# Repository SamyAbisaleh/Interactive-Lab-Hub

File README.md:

# Interactive-Lab-Hub

Completed Labs for Samy Abisaleh -- Student

1. [Samy A's Lab 1](https://github.com/SamyAbisaleh/Interactive-Lab-Hub/tree/master/Lab%201)
2. [Samy A's Lab 2](https://github.com/SamyAbisaleh/Interactive-Lab-Hub/tree/master/Lab%202)
3. [Samy A's Lab 3](https://github.com/SamyAbisaleh/Interactive-Lab-Hub/tree/master/Lab%203)
4. [Samy A's Lab 5](https://github.com/SamyAbisaleh/Interactive-Lab-Hub/tree/master/Alt-Lab%20%235)
5. [Samy A's Lab 6](https://github.com/SamyAbisaleh/Interactive-Lab-Hub/tree/master/Lab-6)
6. [Samy A's Lab 7](https://github.com/SamyAbisaleh/Interactive-Lab-Hub/blob/master/Lab-7)
7. [Samy A's Final Project](https://github.com/SamyAbisaleh/Interactive-Lab-Hub/tree/master/Final%20Project)

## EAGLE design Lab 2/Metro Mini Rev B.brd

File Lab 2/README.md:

# Alt-Lab #2
## Pre-Lab
### Idea Generation
[Click to access the Ideas generated as a PDF ](https://github.com/SamyAbisaleh/Interactive-Lab-Hub/blob/master/Lab%202/Pre-Lab.pdf)
 
## Overview
For this assignment, you are going to 

A) [Design your Arduino+](#part-a-design-your-arduino) 

B) [Order parts for your Arduino+](#part-b-order-parts-for-your-arduino) 

C) [Prototype your Arduino+](#part-c-prototype-your-arduino)

D) [Layout your Arduino+](#part-d-layout-your-arduino) 

E) [Send your board off to be made](#part-e-send-your-board-off-to-be-made)

## Part A. Design your Arduino+
Please document the design of your Arduino+:

**a) What is the + improvement of your Arduino+**
In this repo you will find the original files from Adafruit for the Metro Mini and a file I have edited. You can compare the changes to the schematic and the board file to see which changes were made.

I've decided I want to be able to read the temperature from my Metro Mini and have that be a part of the board itself. This requires adding an Temperature Sensor. I am using a surface mount [component](https://app.ultralibrarian.com/details/1690C20E-103F-11E9-AB3A-0A3560A4CCCC/Texas-Instruments/TMP102AIDRLRG4?ref=digikey)

**b) What Arduino form-factor/design are you basing your design off of?**
* My design is based off of the Metro Mini, the files I started with can be found: [here](https://github.com/SamyAbisaleh/Interactive-Lab-Hub/tree/master/Lab%202/Metro%20Mini%20Files/Adafruit-METRO-328-PCB-master/Adafruit-METRO-328-PCB-master)

**c) What features/parts need to be incorporated for your Arduino+? Include your research!**
Based on the datasheet there are multiple things that needed to be considered and added to my Arduino.
1. The entire Metro Mini must be operating at 3.3 V instead of 5V as the SDA and SCL pins cannot operate at 5V and it may cause damage to the sensor
2. The second important feature that I must incorporate is 2 5K resistors that buffer the SDA and SCL pins from the 3.3 Volts.
3. Finally, I must include a .01 uF capacitor to help prevent noise from impacting the sensor.

The schematic I based these decisions off of can be found below.

**d) What is the timeline for the overall development of your Arduino?**

Based on a quick look at PCBShopper, it seems as though the timeline for the development of my Arduino is about 7 days to be created. Overall the entire project will take about 2-3 weeks to be completed. 1 week to determine what I am working on, and designing what I am working on. 1-2 weeks to order, create, and ship my design.

**e) Which fabrication company are you using, what do you plan to order, and what is the design rationale for the selection?**

I already ordered all my parts and my PCB using the Aisler.net. The total cost was about 15 dollars with shipping. This is expected to come to me in about 1-2 Weeks. I used this selection because it is a US based company (shipping should not be delayed due to COVID), the prices were low (15 dollars for 3 boards), they will put the parts on the board for me (just upload BOM and assign your parts). I was very impressed with how simple the process was, and I hope that everything comes in working condition. 

## Part B. Order parts for your Arduino+

Develop a bill of materials for your Arduino +.

**Bill of Materials**
|   Part  	|           Value          	|           Device          	|             Package            	|            Description           	|                                      Notes                                     	|                                                                                                                                                                     Link to part                                                                                                                                                                    	|
|:-------:	|:------------------------:	|:-------------------------:	|:------------------------------:	|:--------------------------------:	|:------------------------------------------------------------------------------:	|:---------------------------------------------------------------------------------------------------------------------------------------------------------------------------------------------------------------------------------------------------------------------------------------------------------------------------------------------------:	|
|    AD   	|           20609          	|      HEADER-1X6ROUND      	|           1X06_ROUND           	|            PIN HEADER            	|                            Footprint for pin headers                           	| [Link](https://www.digikey.com/product-detail/en/harwin-inc/D01-9923246/952-2521-ND/3918909?utm_adgroup=Rectangular%20Connectors%20-%20Headers%2C%20Specialty%20Pin&utm_source=google&utm_medium=cpc&utm_campaign=Shopping_Product_Connectors%2C%20Interconnects&utm_term=&utm_content=Rectangular%20Connectors%20-%20Headers%2C%20Specialty%20Pin) 	|
|   AD1   	|           20609          	|      HEADER-1X6ROUND      	|           1X06_ROUND           	|            PIN HEADER            	|                            Footprint for pin headers                           	| [Link](https://www.digikey.com/product-detail/en/harwin-inc/D01-9923246/952-2521-ND/3918909?utm_adgroup=Rectangular%20Connectors%20-%20Headers%2C%20Specialty%20Pin&utm_source=google&utm_medium=cpc&utm_campaign=Shopping_Product_Connectors%2C%20Interconnects&utm_term=&utm_content=Rectangular%20Connectors%20-%20Headers%2C%20Specialty%20Pin) 	|
|    C1   	|           10uF           	| CAP_CERAMIC0805-NOOUTLINE 	|             0805-NO            	|        Ceramic Capacitors        	|            Decoupling Capacitor: smoothes longer changes in voltage            	|                                                                                                                        https://www.digikey.com/product-detail/en/GRM21BC81D106KE51L/490-10500-1-ND/5026426/?itemSeq=338642887                                                                                                                       	|
|    C2   	|           10uF           	| CAP_CERAMIC0805-NOOUTLINE 	|             0805-NO            	|        Ceramic Capacitors        	|            Decoupling Capacitor: smoothes longer changes in voltage            	|                                                                                                                        https://www.digikey.com/product-detail/en/GRM21BC81D106KE51L/490-10500-1-ND/5026426/?itemSeq=338642887                                                                                                                       	|
|    C3   	|           10uF           	| CAP_CERAMIC0805-NOOUTLINE 	|             0805-NO            	|        Ceramic Capacitors        	|           Decoupling Capacitor: smoothes longer variation in voltage           	|                                                                                                                        https://www.digikey.com/product-detail/en/GRM21BC81D106KE51L/490-10500-1-ND/5026426/?itemSeq=338642887                                                                                                                       	|
|    C4   	|           0.1uF          	| CAP_CERAMIC0805-NOOUTLINE 	|             0805-NO            	|        Ceramic Capacitors        	|        Decoupling Capacitor: smoothes high frequency changes in voltage        	|                                                                                                                         https://www.digikey.com/product-detail/en/C0805C104M3RACTU/399-8000-6-ND/3472531/?itemSeq=338642888                                                                                                                         	|
|    C5   	|           0.1uF          	|     CAP_CERAMIC_0805MP    	|             _0805MP            	|        Ceramic Capacitors        	| When the DTR changes from high to low the reset pin on the ATMega will go high 	|                                                                                                                         https://www.digikey.com/product-detail/en/C0805C104M3RACTU/399-8000-6-ND/3472531/?itemSeq=338642888                                                                                                                         	|
|    C6   	|           0.1uF          	| CAP_CERAMIC0805-NOOUTLINE 	|             0805-NO            	|        Ceramic Capacitors        	|        Decoupling Capacitor: smoothes high frequency changes in voltage        	|                                                                                                                         https://www.digikey.com/product-detail/en/C0805C104M3RACTU/399-8000-6-ND/3472531/?itemSeq=338642888                                                                                                                         	|
|    C8   	|           0.1uF          	| CAP_CERAMIC0805-NOOUTLINE 	|             0805-NO            	|        Ceramic Capacitors        	|        Decoupling Capacitor: smoothes high frequency changes in voltage        	|                                                                                                                         https://www.digikey.com/product-detail/en/C0805C104M3RACTU/399-8000-6-ND/3472531/?itemSeq=338642888                                                                                                                         	|
|   C10   	|           0.1uF          	| CAP_CERAMIC0805-NOOUTLINE 	|             0805-NO            	|        Ceramic Capacitors        	|        Decoupling Capacitor: smoothes high frequency changes in voltage        	|                                                                                                                         https://www.digikey.com/product-detail/en/C0805C104M3RACTU/399-8000-6-ND/3472531/?itemSeq=338642888                                                                                                                         	|
|   C12   	|           10uF           	| CAP_CERAMIC0805-NOOUTLINE 	|             0805-NO            	|        Ceramic Capacitors        	|            Decoupling Capacitor: smoothes longer changes in voltage            	|                                                                                                                        https://www.digikey.com/product-detail/en/GRM21BC81D106KE51L/490-10500-1-ND/5026426/?itemSeq=338642887                                                                                                                       	|
|   C13   	|           .01uF          	| CAP_CERAMIC0805-NOOUTLINE 	|             0805-NO            	|        Ceramic Capacitors        	|            Decoupling Capacitor: smoothes longer changes in voltage            	|                                                                                                                   https://www.mouser.com/ProductDetail/KEMET/CKC33C103KJGACTU?qs=sGAEpiMZZMuMW9TJLBQkXhX%2FY8cKkU6Pw0elzxufyyw%3D                                                                                                                   	|
|    D3   	|          MBR120          	|   DIODE-SCHOTTKYSOD-123   	|             SOD-123            	|               Diode              	|                           ESD protection for USB port                          	|                                                                                                                     https://www.digikey.com/product-detail/en/BAT60AE6327HTSA1/BAT60AE6327HTSA1CT-ND/1557845/?itemSeq=338642881                                                                                                                     	|
|    D4   	|          YELLOW          	|     LED0805_NOOUTLINE     	|     CHIPLED_0805_NOOUTLINE     	|                LED               	|                                  Indicator LED                                 	|                                                                                                                           https://www.digikey.com/product-detail/en/150080YS75000/732-4987-1-ND/4489925/?itemSeq=338642883                                                                                                                          	|
|    D5   	|          YELLOW          	|     LED0805_NOOUTLINE     	|     CHIPLED_0805_NOOUTLINE     	|                LED               	|                                  Indicator LED                                 	|                                                                                                                           https://www.digikey.com/product-detail/en/150080YS75000/732-4987-1-ND/4489925/?itemSeq=338642883                                                                                                                          	|
|   IOL   	|           20610          	|      HEADER-1X8ROUND      	|           1X08_ROUND           	|            PIN HEADER            	|                            Footprint for pin headers                           	|     https://www.digikey.com/product-detail/en/harwin-inc/D01-9923246/952-2521-ND/3918909?utm_adgroup=Rectangular%20Connectors%20-%20Headers%2C%20Specialty%20Pin&utm_source=google&utm_medium=cpc&utm_campaign=Shopping_Product_Connectors%2C%20Interconnects&utm_term=&utm_content=Rectangular%20Connectors%20-%20Headers%2C%20Specialty%20Pin     	|
|    L    	|            RED           	|     LED0805_NOOUTLINE     	|     CHIPLED_0805_NOOUTLINE     	|                LED               	|                                  Indicator LED                                 	|                                                                                                                           https://www.digikey.com/product-detail/en/LH+R974-LP-1/475-1415-1-ND/1802604/?itemSeq=338642877                                                                                                                           	|
|    ON   	|           GREEN          	|     LED0805_NOOUTLINE     	|     CHIPLED_0805_NOOUTLINE     	|                LED               	|                                  Indicator LED                                 	|                                                                                                                           https://www.digikey.com/product-detail/en/LG+R971-KN-1/475-1410-1-ND/1802598/?itemSeq=338642882                                                                                                                           	|
|  POWER1 	|           20610          	|      HEADER-1X870MIL      	|          1X08_ROUND_70         	|            PIN HEADER            	|                            Footprint for pin headers                           	|     https://www.digikey.com/product-detail/en/harwin-inc/D01-9923246/952-2521-ND/3918909?utm_adgroup=Rectangular%20Connectors%20-%20Headers%2C%20Specialty%20Pin&utm_source=google&utm_medium=cpc&utm_campaign=Shopping_Product_Connectors%2C%20Interconnects&utm_term=&utm_content=Rectangular%20Connectors%20-%20Headers%2C%20Specialty%20Pin     	|
|    R1   	|            5k            	|   RESISTOR0805_NOOUTLINE  	|             0805-NO            	|             Resistors            	|                                                                                	|                                                                                                                             https://www.digikey.com/product-detail/en/vishay-dale/PNM0402E5001BST1/541-1901-1-ND/4341858                                                                                                                            	|
|    R2   	|            1K            	|       RESISTOR_4PACK      	|         RESPACK_4X0603         	|   Resistor Packs (4 resistors)   	|                   4x resistor array to current limit the LEDs                  	|                                                                                                                         https://www.digikey.com/product-detail/en/742C083102JP/742C083102JPCT-ND/1124573/?itemSeq=338642869                                                                                                                         	|
|    R4   	|            5k            	|   RESISTOR0805_NOOUTLINE  	|             0805-NO            	|             Resistors            	|                                                                                	|                                                                                                                             https://www.digikey.com/product-detail/en/vishay-dale/PNM0402E5001BST1/541-1901-1-ND/4341858                                                                                                                            	|
|    R8   	|            10K           	|   RESISTOR0805_NOOUTLINE  	|             0805-NO            	|             Resistors            	|         Pullup resistor on reset pin: when you hit reset pulls pin high        	|                                                                                                                         https://www.digikey.com/product-detail/en/RC0805FR-0710KL/311-10.0KCRCT-ND/730482/?itemSeq=338642870                                                                                                                        	|
|   R11   	|            1K            	|   RESISTOR0805_NOOUTLINE  	|             0805-NO            	|             Resistors            	|           Allows you to use the RX pin on the board over CP2104 chip           	|                                                                                                                          https://www.digikey.com/product-detail/en/RC0805JR-071KL/311-1.0KARCT-ND/731165/?itemSeq=338642876                                                                                                                         	|
|  RESET  	|           KMR2           	|   SWITCH_TACT_SMT4.6X2.8  	|        BTN_KMR2_4.6X2.8        	|         SMT Tact Switches        	|                                  Reset Button                                  	|                                                                                                                                    https://www.digikey.com/product-detail/en/c-k/KMR211GLFS/401-1426-1-ND/550461                                                                                                                                    	|
|    U1   	|        MIC5225-5.0       	|        VREG_SOT23-5       	|             SOT23-5            	| SOT23-5 Fixed Voltage Regulators 	|                              5V Voltage Regulator                              	|                                                                                                                  https://www.digikey.com/product-detail/en/LP2985IM5-5.0%2fNOPB/LP2985IM5-5.0%2fNOPBCT-ND/334983/?itemSeq=338642872                                                                                                                 	|
|    U2   	|        ATMEGA328P        	|         ATMEGA328P        	|            MLF32-TH            	|            ATMEGA 328P           	|                                     BRAINZ                                     	|                                                                                                                         https://www.digikey.com/product-detail/en/ATMEGA328P-MU/ATMEGA328P-MU-ND/1914588/?itemSeq=338642865                                                                                                                         	|
|    U3   	|          CP2104          	|           CP2104          	|         QFN24_4MM_SMSC         	|    CP2104 - USB to UART Bridge   	|                          USB communication with ATMEGA                         	|                                                                                                                          https://www.digikey.com/product-detail/en/CP2104-F03-GMR/336-4146-1-ND/7650425/?itemSeq=338642880                                                                                                                          	|
|    U4   	|        MIC5225-3.3       	|        VREG_SOT23-5       	|             SOT23-5            	| SOT23-5 Fixed Voltage Regulators 	|                              3V Voltage Regulator                              	|                                                                                                                https://www.digikey.com/product-detail/en/LP2985IM5X-3.3%2fNOPB/LP2985IM5X-3.3%2fNOPBCT-ND/3527394/?itemSeq=338642873                                                                                                                	|
|    U5   	| TMP102AIDRLRG4DRL6_TEX-M 	|  TMP102AIDRLRG4DRL6_TEX-M 	|           DRL6_TEX-M           	|                                  	|                                                                                	|                                                                                                                          https://www.digikey.com/product-detail/en/texas-instruments/TMP102AIDRLRG4/296-52785-2-ND/1907044                                                                                                                          	|
| VSELECT 	|                          	|     SOLDERJUMPER_2WAY     	| SOLDERJUMPER_2WAY_OPEN_NOPASTE 	|        2-Way Solder Jumper       	|                                                                                	|                                                                                                                                                                                                                                                                                                                                                     	|
|    X1   	|           20329          	|     USB_MICRO_20329_V2    	|         4UCONN_20329_V2        	|          USB Connectors          	|                                  USB connector                                 	|                                                                                                                           https://www.digikey.com/product-detail/en/amphenol-icc-fci/10103594-0001LF/609-4050-1-ND/2350357                                                                                                                          	|
|    Y2   	|   CSTCE16M0V53-R0 16MHZ  	|        RESONATORMU        	|            RESONATOR           	|                                  	|                             Set ATMEGA clock speed                             	|                                                                                                                        https://www.digikey.com/product-detail/en/CSTNE16M0V530000R0/490-17948-1-ND/8747756/?itemSeq=338642875                                                                                                                       	|

## Part C. Prototype your Arduino+

To prototype my Arduino, I need to order a [Temperature Sensor](https://www.mouser.com/ProductDetail/Adafruit/3251?qs=DJieTMTAD3WAE3SOd7%2FRQw%3D%3D&gclid=CjwKCAjwzIH7BRAbEiwAoDxxTgqD1cUPylyEOXAOaqj2XDN8bReeUK0V1-HSz6L37ovNxTEsysf4IxoC5T8QAvD_BwE). The one that can be found by clicking the link is very similar to my temperature sensor, and is good method of trying out the weather sensor. Everything comes on a PCB, and it comes preinstalled with resistors and ports. It will give me an idea of how I can run the temp-sensor. 

**Describe key design questions (how big are the parts? what pins need to be connected?) and how you used/will use prototyping to answer them.**

The parts are very small, and will fit on a breadboard. I will connect, pins A4 and A5, as well as the pins that connect the weather sensor to 3.3V and GND. This will allow me to prototype my code and determine whether or not it works. Furthermore, it will give me a point of comparison to my own board. Allowing me to determine where I might have gone wrong -- if the board does not work. 

## Part D. Layout your Arduino+
* [Metro Mini official open source layout](https://github.com/SamyAbisaleh/Interactive-Lab-Hub/tree/master/Lab%202/Metro%20Mini%20Files/Adafruit-METRO-328-PCB-master/Adafruit-METRO-328-PCB-master)

* [Temp Sensor Official Layout](https://github.com/SamyAbisaleh/Interactive-Lab-Hub/tree/master/Lab%202/Temp%20Sensor)

* [ My Official Board Layout (On Eagle)](https://github.com/SamyAbisaleh/Interactive-Lab-Hub/blob/master/Lab%202/Metro%20Mini%20Rev%20B.brd)

* [My Official Schematic Layout (On Eagle)](https://github.com/SamyAbisaleh/Interactive-Lab-Hub/blob/master/Lab%202/Metro%20Mini%20Rev%20B.sch)

## Part E. Send your board off to be made

When you have laid out your board, send it off to be fabricated. You might need to order components, tools or other apparatus (like programmers or FTDI interfaces) to complete the design at this time too.

**Document what you sent, and to where, with enough specificity that anyone else could have the same thing made.**

I send the board found under part D. I sent it to Aisler, after determining its sizing. I would really recommend checking out their website, as they made the entire process almost seamless. [Link can be founder here](https://aisler.net/). Furthermore, my board can be found [here](https://aisler.net/p/UBRWSGKI).

## Pain Points
There were a couple of pain points I had with this assignment
* The assignment instruction are a bit unclear, as theres a mix of being told to buy and prototype but also not buy and wait to get it checked

* I don't have any experience using Eagle, and I've never prototyped or designed a board. This was not a huge issue. The issue came when I had to come up with ideas, I wasn't sure what was easy and what was hard, and I didn't have many other ideas to compare them to. 

* Similar to my lack of experience with Eagle, I thought that the Pre-lab wasn't of much help (in the sense that we are coming up with many different ideas). I think in the future, a potentially better Pre-Lab would be to watch, learn, and do a schematic and board based on a video uploaded to YouTube (basically introduce Eagle). And then have say, 4 options for the designable board: IR sensor, Temp sensor, Built-in LCD, DIY. The last option will allow students with experience to do what they want, and the other 3 will help the TA's not have to help everyone without any knowledge of their parts. (Note: there might be a better way to do this, just an idea)

* Overall though, although I found the assignment a bit hard, it was rewarding when I was able to come up with the final parts sketch. I might not be an Eagle Pro but I definitley understand the ins and outs of it a lot better. It also helped me understand how board are made and work a lot better.

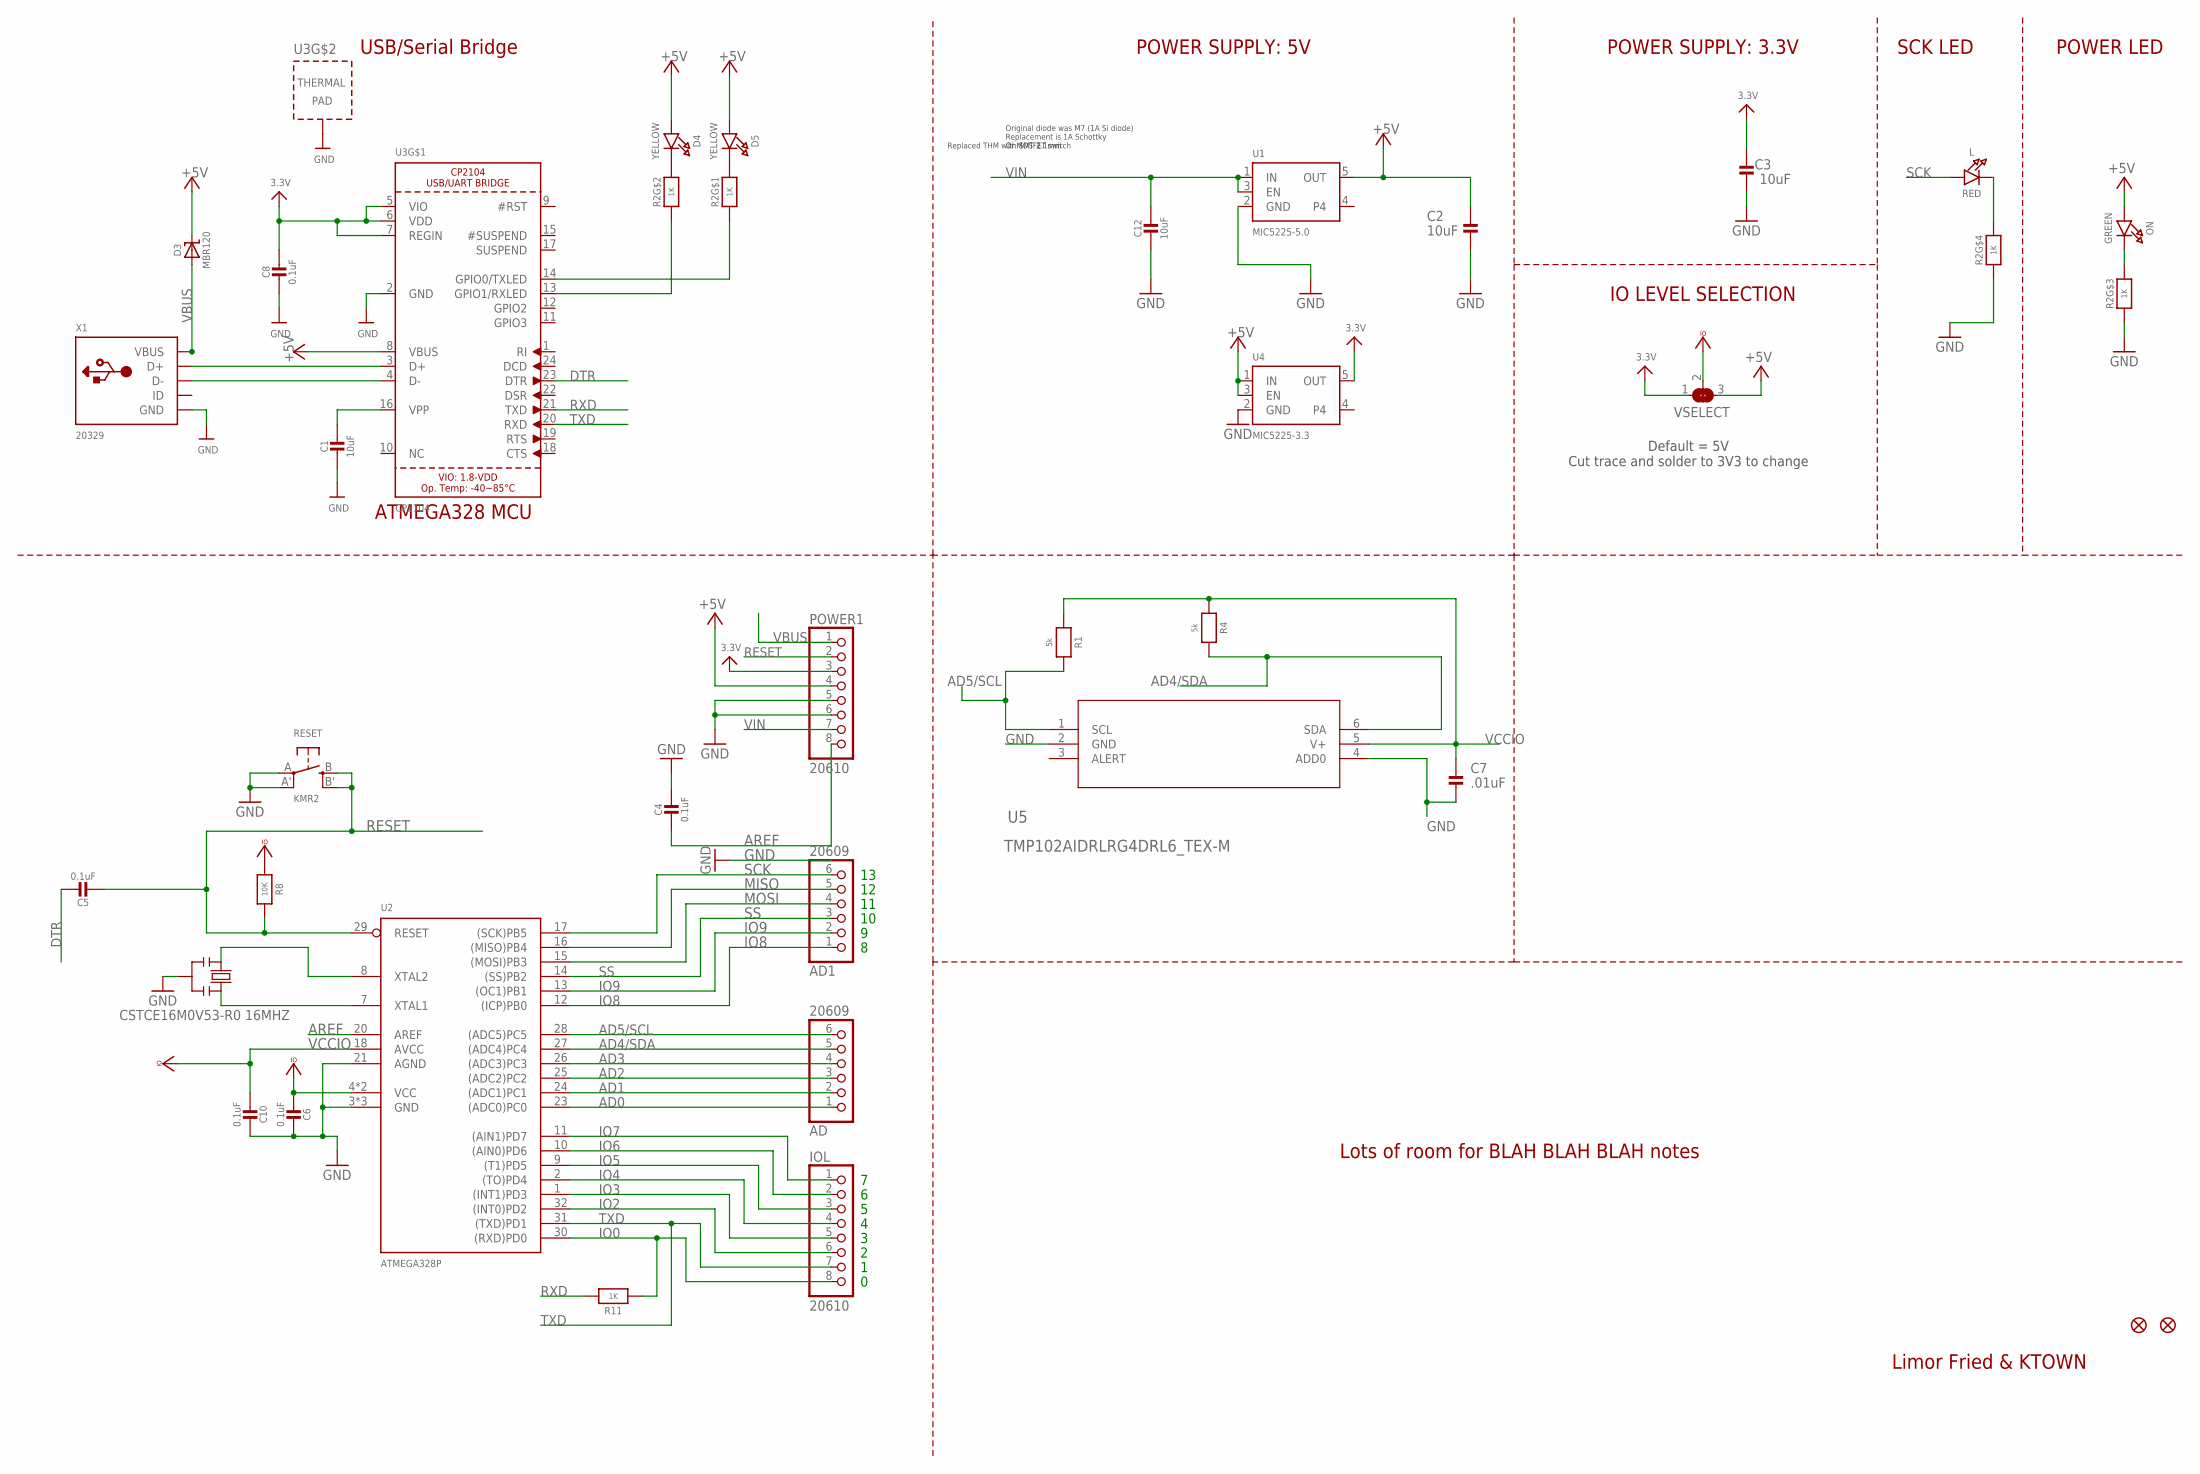
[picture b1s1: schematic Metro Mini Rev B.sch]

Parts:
AD, AD1: 20609; 1X06_ROUND
C1, C2, C3, C12: 10uF; 0805-NO
C4, C6, C8, C10: 0.1uF; 0805-NO
C5: 0.1uF; _0805MP
C7: .01uF; 0805-NO
D3: MBR120; SOD-123
D4, D5: YELLOW; CHIPLED_0805_NOOUTLINE
FD1, FD2: FIDUCIAL""; FIDUCIAL_1MM
IOL: 20610; 1X08_ROUND
L: RED; CHIPLED_0805_NOOUTLINE
ON: GREEN; CHIPLED_0805_NOOUTLINE
POWER1: 20610; 1X08_ROUND_70
R1, R4: 5k; 0805-NO
R2: 1K; RESPACK_4X0603
R8: 10K; 0805-NO
R11: 1K; 0805-NO
RESET: KMR2; BTN_KMR2_4.6X2.8
U1: MIC5225-5.0; SOT23-5
U2: ATMEGA328P; MLF32-TH
U3: CP2104; QFN24_4MM_SMSC
U4: MIC5225-3.3; SOT23-5
U5: TMP102AIDRLRG4DRL6_TEX-M; DRL6_TEX-M
VSELECT: SOLDERJUMPER_2WAY; SOLDERJUMPER_2WAY_OPEN_NOPASTE
X1: 20329; 4UCONN_20329_V2
Y2: CSTCE16M0V53-R0 16MHZ; RESONATOR

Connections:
3.3V: C3.2, C8.1, POWER1.3, U3.5 (VIO), U3.6 (VDD), U3.7 (REGIN), U4.5 (OUT), VSELECT.1
+5V: C2.2, D3.C, D4.A, D5.A, ON.A, POWER1.4, U1.5 (OUT), U3.8 (VBUS), U4.1 (IN), U4.3 (EN), VSELECT.3
AD0: AD.1, U2.23 ((ADC0)PC0)
AD1: AD.2, U2.24 ((ADC1)PC1)
AD2: AD.3, U2.25 ((ADC2)PC2)
AD3: AD.4, U2.26 ((ADC3)PC3)
AD4/SDA: AD.5, R4.2, U2.27 ((ADC4)PC4), U5.6 (SDA)
AD5/SCL: AD.6, R1.2, U2.28 ((ADC5)PC5), U5.1 (SCL)
AREF: C4.2, POWER1.8, U2.20 (AREF)
DTR: C5.1, U3.23 (DTR)
GND: C1.2, C2.1, C3.1, C4.1, C6.1, C7.1, C8.2, C10.1, C12.2, POWER1.5, POWER1.6, R2.3 (1), R2.4 (1), RESET.A, RESET.A' (P1), U1.2 (GND), U2.3 (GND), U2.5 (GND), U2.21 (AGND), U2.TH (GND), U3.2 (GND), U3.THERM (TP), U4.2 (GND), U5.2 (GND), U5.4 (ADD0), X1.BASE@1 (GND), X1.BASE@2 (GND), X1.GND, X1.SPRT@1 (GND), X1.SPRT@2 (GND), X1.SPRT@3 (GND), X1.SPRT@4 (GND), Y2.2
IO0: IOL.8, R11.1, U2.30 ((RXD)PD0)
IO2: IOL.6, U2.32 ((INT0)PD2)
IO3: IOL.5, U2.1 ((INT1)PD3)
IO4: IOL.4, U2.2 ((TO)PD4)
IO5: IOL.3, U2.9 ((T1)PD5)
IO6: IOL.2, U2.10 ((AIN0)PD6)
IO7: IOL.1, U2.11 ((AIN1)PD7)
IO8: AD1.1, U2.12 ((ICP)PB0)
IO9: AD1.2, U2.13 ((OC1)PB1)
MISO: AD1.5, U2.16 ((MISO)PB4)
MOSI: AD1.4, U2.15 ((MOSI)PB3)
unnamed: L.C, R2.5 (2)
unnamed: ON.C, R2.6 (2)
unnamed: R2.1, U3.14 (GPIO0/TXLED)
unnamed: D4.C, R2.7 (2)
unnamed: D5.C, R2.8 (2)
unnamed: U3.3 (D+), X1.D+
unnamed: U3.4 (D-), X1.D-
unnamed: C1.1, U3.16 (VPP)
unnamed: R2.2 (1), U3.13 (GPIO1/RXLED)
RESET: C5.2, POWER1.2, R8.1, RESET.B (S), RESET.B' (S1), U2.29 (RESET)
RXD: R11.2, U3.21 (TXD)
SCK: AD1.6, L.A, U2.17 ((SCK)PB5)
SS: AD1.3, U2.14 ((SS)PB2)
TXD: IOL.7, U2.31 ((TXD)PD1), U3.20 (RXD)
VBUS: D3.A, POWER1.1, X1.VBUS
VCCIO: C6.2, C7.2, C10.2, R1.1, R4.1, R8.2, U2.4 (VCC), U2.6 (VCC), U2.18 (AVCC), U5.5 (V+), VSELECT.2
VIN: C12.1, POWER1.7, U1.1 (IN), U1.3 (EN)
XTAL1: U2.7 (XTAL1), Y2.3
XTAL2: U2.8 (XTAL2), Y2.1

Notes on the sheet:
Limor Fried & KTOWN
Original diode was M7 (1A Si diode) Replacement is 1A Schottky Or MOSFET switch
Replaced THM with SMT 2.1mm
POWER SUPPLY: 5V
USB/Serial Bridge
POWER SUPPLY: 3.3V
IO LEVEL SELECTION
POWER LED
ATMEGA328 MCU
SCK LED
Lots of room for BLAH BLAH BLAH notes
Default = 5V Cut trace and solder to 3V3 to change

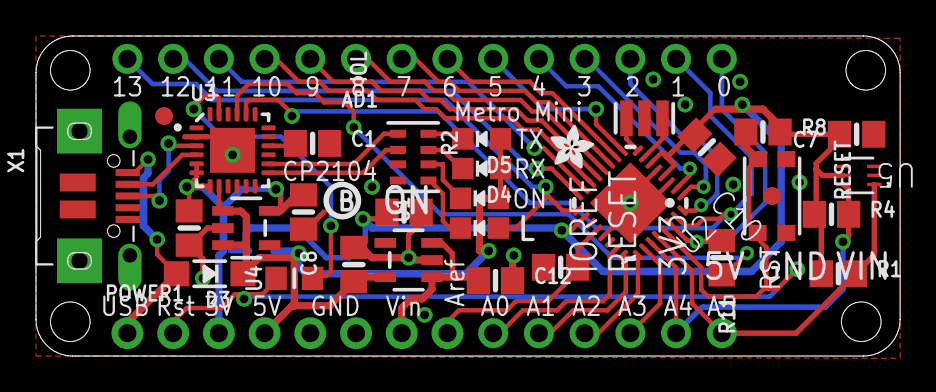
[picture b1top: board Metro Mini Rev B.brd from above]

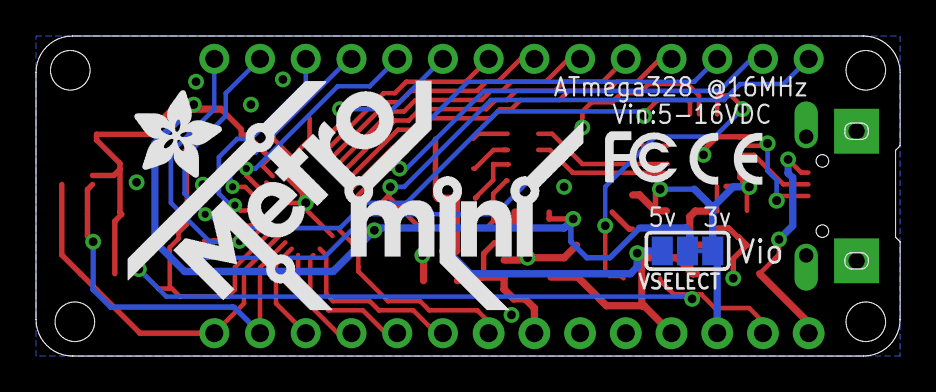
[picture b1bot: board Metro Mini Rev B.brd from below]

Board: 2 copper layers, 48.0 x 17.8 mm, 41 parts (5 on the bottom side), 41 nets.

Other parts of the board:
U$4: PCBFEAT-REV-040
U$5: ADAFRUIT_2.5MM
U$7: METROMINI_SILK
U$10: ADAFRUIT_5MM
U$12: SYMBOL_CE_TINY
U$14: SYMBOL_FCC_TINY

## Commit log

2020-09-05 Create Lab 1
2020-09-05 Rename Lab 1 to Lab 1.md
2020-09-05 Rename Lab 1.md to Lab 1/Read Me Lab 1.md
2020-09-14 Create Metro mini foloder
2020-09-14 Rename Alt Lab 2 Read Me.md to README.md
2020-10-12 Rename Lab 1/README.md to Alt-lab 1/README.md
2020-10-12 Rename Alt-lab 1/README.md to Lab 1/README.md
2020-12-17 Create Final Write-Up

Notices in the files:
parts and their libraries:
microbuilder: This work is placed in the public domain, and may be freely used for commercial and non-commercial work with the following conditions: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
COPYRIGHT: Copyright (C) 2018 Accelerated Designs. All rights reserved
